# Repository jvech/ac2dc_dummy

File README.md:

# AC to DC

This is the simplest AC to DC converter I can think of

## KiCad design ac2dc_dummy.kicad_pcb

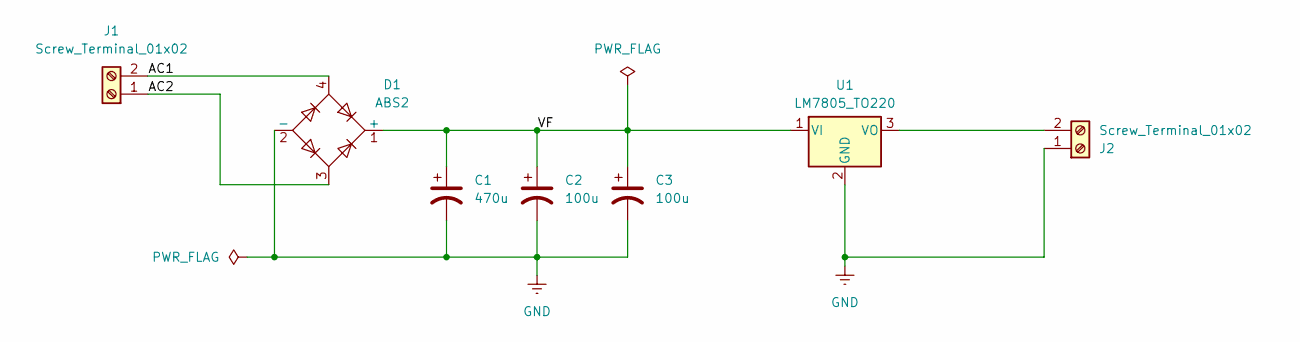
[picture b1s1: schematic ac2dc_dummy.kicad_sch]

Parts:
C1: 470u; C_Radial_D12.5mm_H20.0mm_P5.00mm
C2, C3: 100u; C_Radial_D6.3mm_H11.0mm_P2.50mm
D1: ABS2; Diode_Bridge_Diotec_ABS
J1, J2: Screw_Terminal_01x02; TerminalBlock_Altech_AK300-2_P5.00mm
U1: LM7805_TO220; TO-220-3_Vertical

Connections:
/AC1: D1.4, J1.2
/AC2: D1.3, J1.1
/VF: C1.1, C2.1, C3.1, D1.1 (+), U1.1 (VI)
GND: C1.2, C2.2, C3.2, D1.2 (-), J2.1, U1.2 (GND)
unnamed: J2.2, U1.3 (VO)

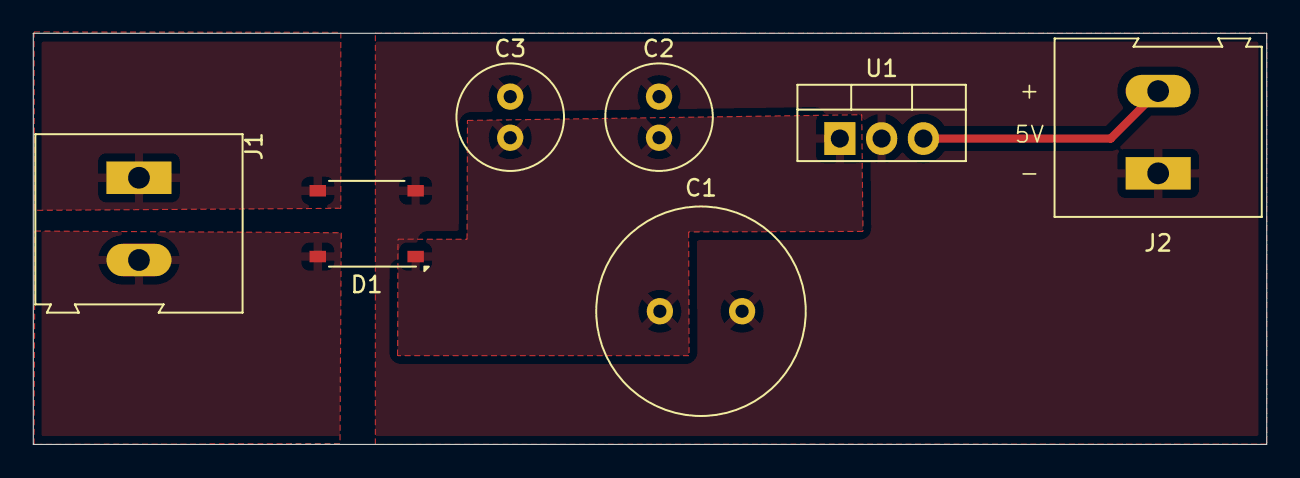
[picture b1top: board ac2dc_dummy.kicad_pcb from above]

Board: 2 copper layers, 75.0 x 25.0 mm, 7 parts (0 on the bottom side), 5 nets.

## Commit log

2024-06-11 init: simple kicad project done
